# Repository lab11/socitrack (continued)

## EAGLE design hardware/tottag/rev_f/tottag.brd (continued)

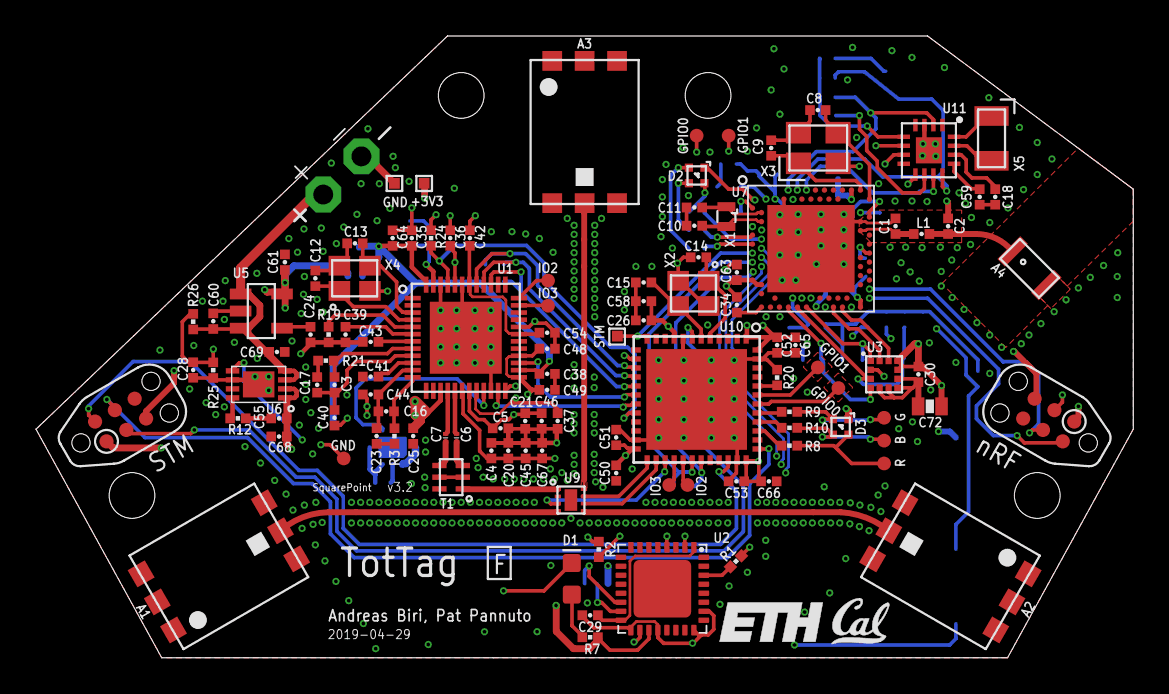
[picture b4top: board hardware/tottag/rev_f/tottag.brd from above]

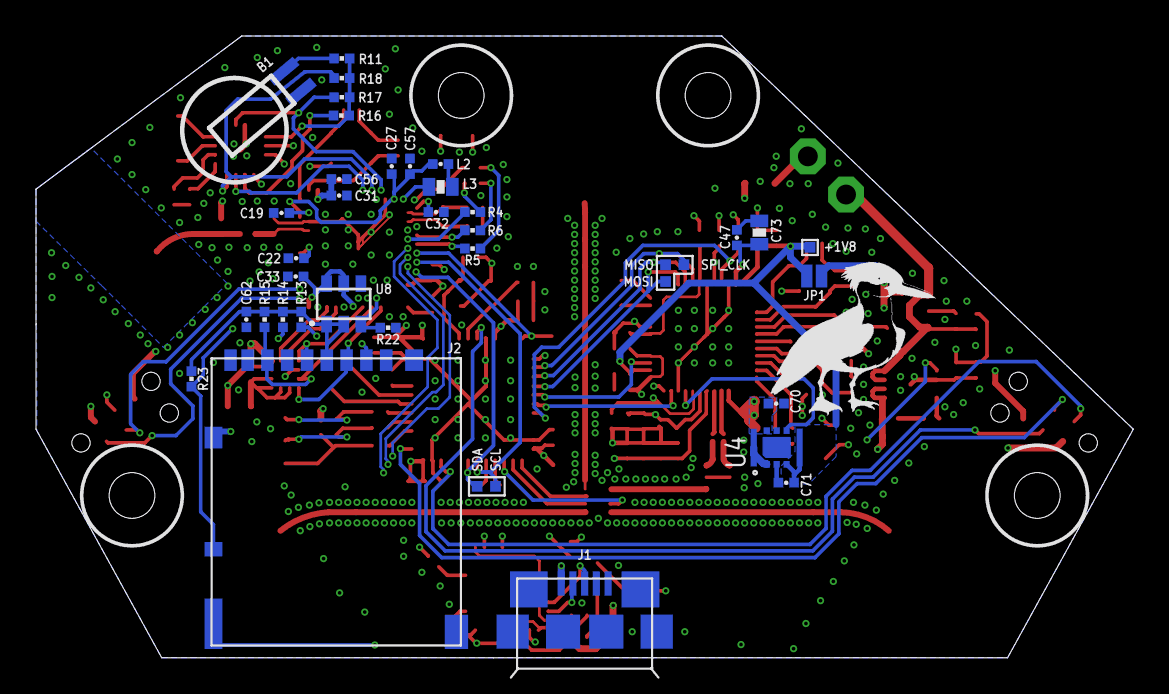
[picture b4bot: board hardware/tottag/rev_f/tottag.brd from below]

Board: 4 copper layers, 61.0 x 34.5 mm, 157 parts (40 on the bottom side), 116 nets.

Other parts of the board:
U$1: TOTTERNARY_300MIL
U$3: ETH_200MIL
U$4: UCB_CAL_100MIL

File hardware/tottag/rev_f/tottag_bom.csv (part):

Qty,Parts,Value,Can Substitute,Do not populate (DNP),Device,Package,Description,DESCRIPTION,DIGIKEY,MANUFACTURER,MPN,MOUSER,Notes
3,"A1,A2,A3",TAIYO-YUDEN-AH086M,N,,TAIYO-YUDEN-AH086M,TAIYO-YUDEN-AH086M,UWB Antenna - 3.1-8GHz,RF ANT 3.5GHZ/5.6GHZ CHIP SLD,587-2204-1-ND,Taiyo Yuden,AH086M555003-T,,
1,A4,ANT3216A063R2400A,N,,ANT3216A063R2400A,ANT3216A063R2400A,Yageo 2.4GHz,RF ANT 2.4GHZ CHIP SOLDER SMD,311-1542-1-ND,Yageo,ANT3216A063R2400A,,
2,"C1,C2",1pF,Y,,CAPACITOR0402_CAP,0402_CAP,SMD Capacitor,CAP CER 1PF 50V C0G/NP0 0402,712-1266-1-ND,Johanson Technology Inc.,500R07S1R0BV4T,,
1,C3,1.2pF,N,,CAPACITOR0402_CAP,0402_CAP,SMD Capacitor,CAP CER 1.2PF 50V C0G/NP0 0402,490-3085-1-ND,Murata Electronics North America,GJM1555C1H1R2CB01D,,
2,"C4,C5",10pF,Y,,CAPACITOR0402_CAP,0402_CAP,SMD Capacitor,CAP CER 10PF 100V C0G/NP0 0402,732-12054-1-ND,Wurth Electronics Inc.,885012005074,,
2,"C6,C7",12pF,N,,CAPACITOR0201_CAP,0201_CAP,SMD Capacitor,CAP CER 12PF 25V C0G/NP0 0201,712-1208-1-ND,Johanson Technology Inc.,250R05L120GV4T,,
8,"C8,C9,C10,C11,C12,C13,C14,C15",12pF,N,,CAPACITOR0402_CAP,0402_CAP,SMD Capacitor,CAP CER 12PF 50V C0G/NP0 0402,490-11190-1-ND,Murata Electronics North America,GJM1555C1H120FB01D,,
1,C16,18pF,N,,CAPACITOR0402_CAP,0402_CAP,SMD Capacitor,CAP CER 18PF 50V C0G/NP0 0402,399-8828-1-ND,KEMET,CBR04C180F5GAC,,
1,C17,27pF,N,,CAPACITOR0402_CAP,0402_CAP,SMD Capacitor,CAP CER 27PF 50V C0G/NP0 0402,490-16380-1-ND,Murata Electronics North America,GJM1555C1H270FB01D,,
1,C18,100pF,Y,,CAPACITOR0402_CAP,0402_CAP,SMD Capacitor,CAP CER SMD 0402 100PF 5% X7R 50,399-17545-1-ND,KEMET,C0402C101J5RACAUTO,,
2,"C19,C20",330pF,Y,,CAPACITOR0402_CAP,0402_CAP,SMD Capacitor,CAP CER 330PF 50V X7R 0402,311-3768-1-ND,Yageo,CC0402JRX7R9BB331,,
2,"C21,C22",820pF,N,,CAPACITOR0402_CAP,0402_CAP,SMD Capacitor,CAP CER 820PF 25V NP0 0402,399-15345-1-ND,KEMET,C0402C821J3GAC7867,,
3,"C23,C24,C25",10nF,Y,,CAPACITOR0402_CAP,0402_CAP,SMD Capacitor,CAP CER 10000PF 25V X7R 0402,399-1279-1-ND,KEMET,C0402C103J3RACTU,,
1,C26,47nF,Y,,CAPACITOR0402_CAP,0402_CAP,SMD Capacitor,CAP CER 0.047UF 16V X7R 0402,445-1264-1-ND,TDK Corporation,C1005X7R1C473K050BC,,
27,"C27,C28,C29,C30,C31,C32,C33,C34,C35,C36,C37,C38,C39,C40,C41,C42,C43,C44,C45,C46,C47,C48,C49,C50,C51,C52,C53",0.1uF,Y,,CAPACITOR0402_CAP,0402_CAP,SMD Capacitor,CAP CER 0.1UF 16V X5R 0402,1276-1234-1-ND,Samsung Electro-Mechanics,CL05A104KO5NNNC,,
4,"C54,C55,C56,C57",1uF,Y,,CAPACITOR0402_CAP,0402_CAP,SMD Capacitor,CAP CER 1UF 10V X6S 0402,1276-6805-1-ND,Samsung Electro-Mechanics,CL05X105KP5NNNC,,
11,"C58,C59,C60,C61,C62,C63,C64,C65,C66,C67,C68",4.7uF,Y,,CAPACITOR0402_CAP,0402_CAP,SMD Capacitor,CAP CER 4.7UF 10V X5R 0402,490-14306-1-ND,Murata Electronics North America,GRM155R61A475MEAAD,,
2,"C69,C70",10uF,Y,,CAPACITOR0603_CAP,0603_CAP,SMD Capacitor,CAP CER 10UF 10V X5R 0603,490-10474-1-ND,Murata Electronics North America,GRM188R61A106KE69D,,
1,C71,47uF,Y,,CAPACITOR0603_CAP,0603_CAP,SMD Capacitor,CAP CER 47UF 6.3V X5R 0603,490-13247-1-ND,Murata Electronics North America,GRM188R60J476ME15D,81-GRM188R60J476ME5D,
1,D1,GREEN,Y,,LED0603,LED-0603,LED (Generic),LED GREEN CLEAR SMD,160-1446-1-ND,Lite-On Inc.,LTST-C191KGKT,,
2,"D2,D3",SML-LX0404SIUPGUSB,Y,,SML-LX0404SIUPGUSB,1MM_SQ_4PAD,1mm^2 RGB LED,LED RGB CLEAR SMD,67-2125-1-ND,Lumex Opto/Components Inc.,SML-LX0404SIUPGUSB,,
1,J1,MICRO_USB_B_HIROSE_ZX62-B-5PA(11),N,,MICRO_USB_B_HIROSE_ZX62-B-5PA(11),USB_MICRO_B-HIROSE-ZX62-B-5PA(11),"Connector Receptacle USB - micro B 2.0 5 Position Surface Mount, Right Angle, Horizontal",CONN MICRO SD CARD PUSH-PUSH R/A,HR1964CT-ND,Hirose Electric Co Ltd,DM3AT-SF-PEJM5,,
1,J2,CON_MICRO_SDDM3AT-SF-PEJM5,N,,CON_MICRO_SDDM3AT-SF-PEJM5,DM3AT-SF-PEJM5,CONN MICRO SD R/A PUSH-PUSH SMD,CONN RCPT USB MICRO B SMD R/A,H125270CT-ND,Hirose Electric Co Ltd,ZX62-B-5PA(33),,
1,L1,3.9nH,Y,,INDUCTOR0402,0402_CAP,A very specific inductor,FIXED IND 3.9NH 840MA 66 MOHM,AISC-0402-3N9G-TCT-ND,Abracon LLC,AISC-0402-3N9G-T,,
1,L2,15nH,Y,,INDUCTOR0402,0402_CAP,A very specific inductor,FIXED IND 15NH 320MA 460 MOHM,587-1521-1-ND,Taiyo Yuden,HK100515NJ-T,,
1,L3,10uH,Y,,INDUCTOR0603,0603_CAP,A very specific inductor,FIXED IND 10UH 300MA 600 MOHM,445-6755-1-ND,TDK Corporation,MLZ1608N100LT000,,
2,"R1,R2",0,Y,,RESISTOR0402_RES,0402_RES,Resistor,RES SMD 0 OHM JUMPER 1/10W 0402,P0.0JCT-ND,Panasonic Electronic Components,ERJ-2GE0R00X,,
1,R3,270,N,,RESISTOR0402_RES,0402_RES,Resistor,RES SMD 270 OHM 1% 1/16W 0402,1276-3970-1-ND,Samsung Electro-Mechanics,RC1005F271CS,,
3,"R4,R5,R6",470,Y,,RESISTOR0402_RES,0402_RES,Resistor,RES SMD 470 OHM 1% 1/16W 0402,541-4072-1-ND,Vishay Dale,CRCW0402470RFKEDC,,
4,"R7,R8,R9,R10",1k,Y,,RESISTOR0402_RES,0402_RES,Resistor,RES SMD 1K OHM 1% 1/5W 0402,541-3240-1-ND,Vishay Dale,RCA04021K00FKEDHP,,
1,R11,2k 1%,Y,,RESISTOR0402_RES,0402_RES,Resistor,RES SMD 2K OHM 1% 1/10W 0402,P2.00KLCT-ND,Panasonic Electronic Components,ERJ-2RKF2001X,,
3,"R12,R13,R14",10k,Y,,RESISTOR0402_RES,0402_RES,Resistor,RES SMD 10K OHM 5% 1/10W 0402,P10KJCT-ND,Panasonic Electronic Components,ERJ-2GEJ103X,,
2,"R15,R16",11k 1%,Y,,RESISTOR0402_RES,0402_RES,Resistor,RES SMD 11K OHM 1% 1/10W 0402,P11.0KLCT-ND,Panasonic Electronic Components,ERJ-2RKF1102X,,
1,R17,16k,N,,RESISTOR0402_RES,0402_RES,Resistor,RES SMD 16K OHM 1% 1/16W 0402,YAG5263CT-ND,Yageo,AC0402FR-0716KL,,
3,"R18,R19,R20",100k,Y,,RESISTOR0402_RES,0402_RES,Resistor,RES SMD 100K OHM 1% 1/16W 0402,541-3960-1-ND,Vishay Dale,CRCW0402100KFKEDC,,
1,R21,2.2M,Y,,RESISTOR0402_RES,0402_RES,Resistor,RES SMD 2.2M OHM 1% 1/16W 0402,541-4083-1-ND,Vishay Dale,CRCW04022M20FKEDC,,
1,R22,10M,Y,,RESISTOR0402_RES,0402_RES,Resistor,RES SMD 10M OHM 5% 1/10W 0402,P10MJCT-ND,Panasonic Electronic Components,ERJ-2GEJ106X,,
1,T1,HHM1595A1,N,,HHM1595A1,EIA-0805,"Description: Symbol for HHM1595A1, a multilayer Balun from TDK.",XFMR BALUN RF 3.0-8.0GHZ UWB SMD,445-3387-1-ND,TDK Corporation,HHM1595A1,,
1,U1,DW1000,N,,DW1000,QFN-48-DW1000,"Description: The DecaWave DW1000 chip, used for UWB two-way ranging.",IC RF TXRX 802.15.4 48-QFN,1479-1001-1-ND,Decawave Limited,DW1000-I-TR13,,
1,U2,FT232RQ,N,,FT232RQ,QFN32,Source: http://www.ftdichip.com/Documents/DataSheets/DS_FT232R_v104.pdf,IC USB FS SERIAL UART 32-QFN,768-1008-1-ND,"FTDI, Future Technology Devices International Ltd",FT232RQ,,
1,U3,LIS2DW12,N,,LIS2DW12,LGA-12,ultra low power 3 axis accelerometer,MEMS DIGITAL OUTPUT MOTION SENSOR,497-17718-6-ND,STMicroelectronics,LIS2DW12TR,,
1,U4,LXDC2HN18A,N,,LXDC2HN18A,LXDC2HN,"Description: Symbol for LXDC2HN18A-097, a DC-DC converter by Murata Electronics.",DC/DC CONVERTER SMD,490-12092-1-ND,Murata Electronics North America,LXDC2HN18A-097,,
1,U5,MAX8887EZK33+T,N,,MAX8887EZK33+T,SOT-23-5,IC REG LDO 3.3V 0.3A TSOT23-5,IC REG LIN 3.3V 300MA TSOT23-5,MAX8887EZK33+TCT-ND,Maxim Integrated,MAX8887EZK33+T,,
1,U6,MCP73831,N,,MCP73831,DFN-8-MCP,"Description: Device for MCP73831, a battery charge controller from Microchip.",IC CONTROLLER LI-ION 4.2V 8DFN,MCP73831T-2ACI/MCCT-ND,Microchip Technology,MCP73831T-2ACI/MC,,
1,U7,NRF52840,N,,NRF52840,AQFN73,"ultra-low power 2.4 GHz wireless system on chip (SoC) integrating a multiprotocol 2.4 GHz transceiver, an ARM® Cortex®-M4F CPU.",NRF52840-QIAA QFN 73L,1490-1071-1-ND,Nordic Semiconductor ASA,NRF52840,,
1,U8,SIP32510,N,,SIP32510,TSOT23-6,"Load switch, slew rate controlled. By Vishay",IC LOAD SWITCH SOT23-6, SIP32510DT-T1-GE3CT-ND,Vishay Siliconix,SIP32510DT-T1-GE3,,
1,U9,SKY13317,N,,SKY13317,MLPQ-UT-8,"Description: Device for SKY13317-373LF, an RF switch from Skyworks Inc.",IC SWITCH RF SP3T 8-MLP,863-1056-1-ND,Skyworks Solutions Inc.,SKY13317-373LF,,
1,U10,STM32F091CC,N,,STM32F091CC,UFQFPN-48,"Description: STM32F091CC from STMicroelectronics, an ARM-based 32-bit MCU with 256 kB Flash, 32kB of SRAM and a Cortex M0",IC MCU 32BIT 256KB FLASH 48QFPN,497-15813-ND,STMicroelectronics,STM32F091CCU6,,
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
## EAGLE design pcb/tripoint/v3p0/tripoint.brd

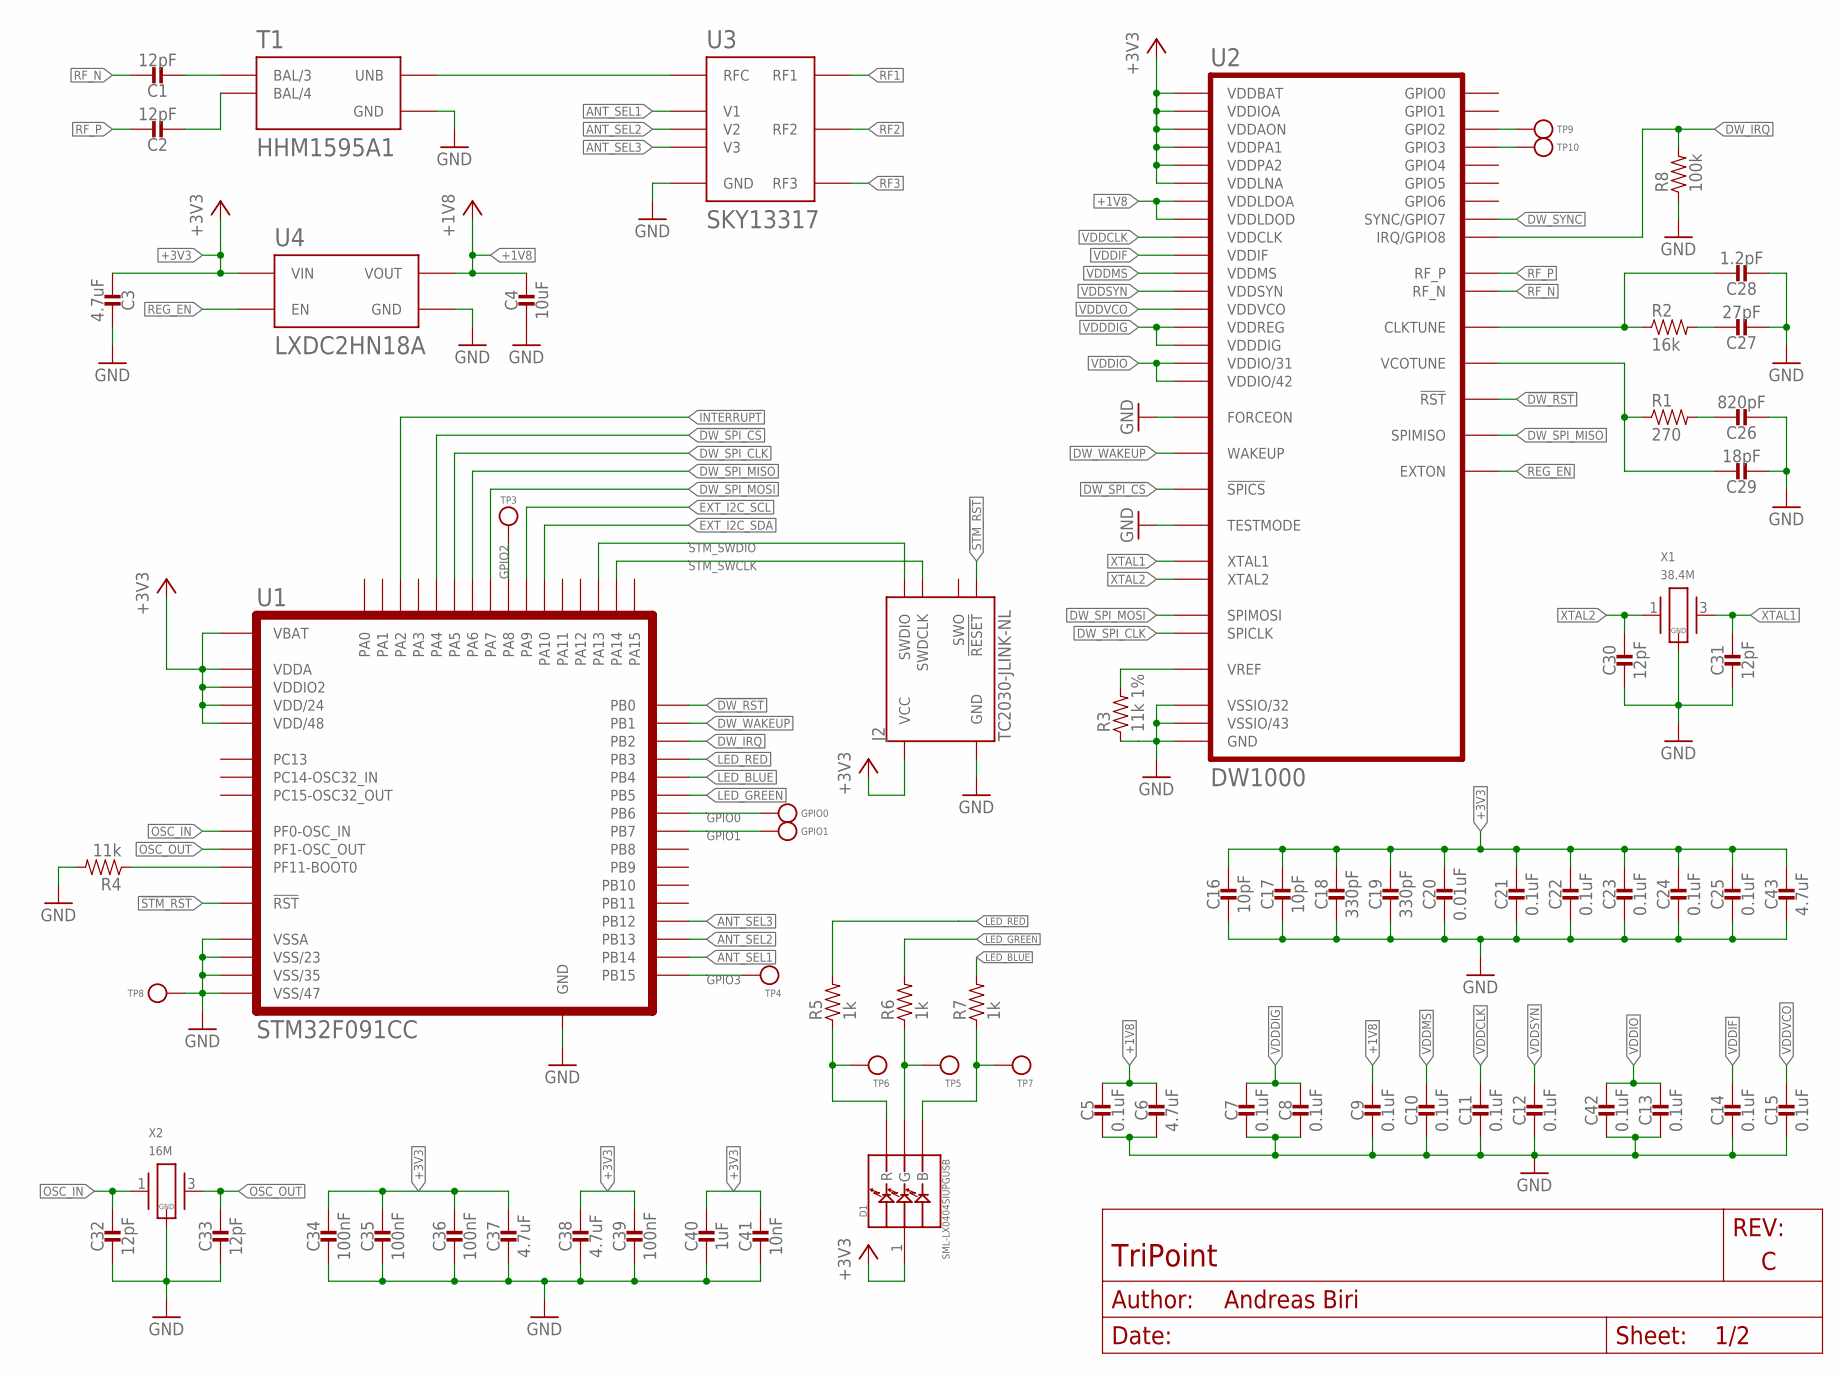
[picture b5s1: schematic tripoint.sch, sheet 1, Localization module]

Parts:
C1, C2: 12pF; 0201_CAP
C3, C6, C37, C38, C43: 4.7uF; 0402_CAP
C4: 10uF; 0603_CAP
C5, C7, C8, C9, C10, C11, C12, C13, C14, C15, C21, C22, C23, C24, C25, C42: 0.1uF; 0402_CAP
C16, C17: 10pF; 0402_CAP
C18, C19: 330pF; 0402_CAP
C20: 0.01uF; 0402_CAP
C26: 820pF; 0402_CAP
C27: 27pF; 0402_CAP
C28: 1.2pF; 0402_CAP
C29: 18pF; 0402_CAP
C30, C31, C32, C33: 12pF; 0402_CAP
C34, C35, C36, C39: 100nF; 0402_CAP
C40: 1uF; 0402_CAP
C41: 10nF; 0402_CAP
D1: SML-LX0404SIUPGUSB; 1MM_SQ_4PAD
GPIO0, GPIO1: TEST_POINT_0.040IN; TESTPOINT_0.040IN
J2: TC2030-JLINK-NL; TC2030-IDC-NL
R1: 270; 0402_RES
R2: 16k; 0402_RES
R3: 11k 1%; 0402_RES
R4: 11k; 0402_RES
R5, R6, R7: 1k; 0402_RES
R8: 100k; 0402_RES
T1: HHM1595A1; EIA-0805
TP3, TP4, TP5, TP6, TP7, TP8, TP9, TP10: TEST-POINT; PAD.03X.03
U1: STM32F091CC; UFQFPN-48
U2: DW1000; QFN-48-DW1000
U3: SKY13317; MLPQ-UT-8
U4: LXDC2HN18A; LXDC2HN
X1: 38.4M; FA-20H; DIGIKEY SER3631CT-ND
X2: 16M; FA-20H; DIGIKEY SER3913CT-ND

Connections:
!DW_RST: U1.18 (PB0), U2.27 (!RST)
!DW_SPI_CS: U1.14 (PA4), U2.24 (!SPICS)
!STM_RST: J2.3 (!RESET), U1.7 (!RST)
+1V8: C4.1, C5.1, C6.1, C9.1, U2.26 (VDDLDOD), U2.48 (VDDLDOA), U4.3 (VOUT)
+3V3: C3.2, C16.1, C17.1, C18.1, C19.1, C20.1, C21.1, C22.1, C23.1, C24.1, C25.1, C34.1, C35.1, C36.1, C37.1, C38.1, C39.1, C40.1, C41.1, C43.1, D1.1 (VDD), J2.1 (VCC), U1.1 (VBAT), U1.9 (VDDA), U1.24 (VDD/24), U1.36 (VDDIO2), U1.48 (VDD/48), U2.15 (VDDLNA), U2.18 (VDDPA1), U2.19 (VDDPA2), U2.25 (VDDAON), U2.28 (VDDIOA), U2.47 (VDDBAT), U4.1 (VIN)
ANT_SEL1: U1.27 (PB14), U3.3 (V1)
ANT_SEL2: U1.26 (PB13), U3.6 (V2)
ANT_SEL3: U1.25 (PB12), U3.7 (V3)
DW_IRQ: R8.2, U1.20 (PB2), U2.45 (IRQ/GPIO8)
DW_SPI_CLK: U1.15 (PA5), U2.41 (SPICLK)
DW_SPI_MISO: U1.16 (PA6), U2.40 (SPIMISO)
DW_SPI_MOSI: U1.17 (PA7), U2.39 (SPIMOSI)
DW_SYNC: U2.29 (SYNC/GPIO7)
DW_WAKEUP: U1.19 (PB1), U2.23 (WAKEUP)
EXT_I2C_SCL: U1.30 (PA9)
EXT_I2C_SDA: U1.31 (PA10)
GND: C3.1, C4.2, C5.2, C6.2, C7.2, C8.2, C9.2, C10.2, C11.2, C12.2, C13.2, C14.2, C15.2, C16.2, C17.2, C18.2, C19.2, C20.2, C21.2, C22.2, C23.2, C24.2, C25.2, C26.2, C27.2, C28.2, C29.2, C30.2, C31.2, C32.2, C33.2, C34.2, C35.2, C36.2, C37.2, C38.2, C39.2, C40.2, C41.2, C42.2, C43.2, J2.5 (GND), R3.1, R4.2, R8.1, T1.2 (GND), T1.5 (GND), TP8.P$1, U1.8 (VSSA), U1.23 (VSS/23), U1.35 (VSS/35), U1.47 (VSS/47), U1.GND, U2.22 (FORCEON), U2.32 (VSSIO/32), U2.43 (VSSIO/43), U2.46 (TESTMODE), U2.GND, U3.GND, U4.4 (GND), X1.2 (GND), X1.4 (GND), X2.2 (GND), X2.4 (GND)
GPIO0: GPIO0.TESTPOINT, U1.42 (PB6)
GPIO1: GPIO1.TESTPOINT, U1.43 (PB7)
GPIO2: TP3.P$1, U1.29 (PA8)
GPIO3: TP4.P$1, U1.28 (PB15)
INTERRUPT: U1.12 (PA2)
LED_BLUE: R7.2, U1.40 (PB4)
LED_GREEN: R6.2, U1.41 (PB5)
LED_RED: R5.2, U1.39 (PB3)
unnamed: T1.1 (UNB), U3.1 (RFC)
unnamed: C1.P$2 (2), T1.3 (BAL/3)
unnamed: C2.P$2 (2), T1.4 (BAL/4)
unnamed: C26.1, R1.2
unnamed: C27.1, R2.2
unnamed: C29.1, R1.1, U2.12 (VCOTUNE)
unnamed: R3.2, U2.5 (VREF)
unnamed: R4.1, U1.44 (PF11-BOOT0)
unnamed: C28.1, R2.1, U2.8 (CLKTUNE)
unnamed: D1.4 (G), R6.1, TP5.P$1
unnamed: D1.3 (B), R7.1, TP7.P$1
unnamed: D1.2 (R), R5.1, TP6.P$1
unnamed: TP9.P$1, U2.36 (GPIO2)
unnamed: TP10.P$1, U2.35 (GPIO3)
OSC_IN: C32.1, U1.5 (PF0-OSC_IN), X2.1
OSC_OUT: C33.1, U1.6 (PF1-OSC_OUT), X2.3 (2)
REG_EN: U2.21 (EXTON), U4.2 (EN)
RF1: U3.4 (RF1)
RF2: U3.5 (RF2)
RF3: U3.8 (RF3)
RF_N: C1.P$1 (1), U2.17 (RF_N)
RF_P: C2.P$1 (1), U2.16 (RF_P)
STM_SWCLK: J2.4 (SWDCLK), U1.37 (PA14)
STM_SWDIO: J2.2 (SWDIO), U1.34 (PA13)
VDDCLK: C11.1, U2.9 (VDDCLK)
VDDDIG: C7.1, C8.1, U2.20 (VDDREG), U2.44 (VDDDIG)
VDDIF: C14.1, U2.7 (VDDIF)
VDDIO: C13.1, C42.1, U2.31 (VDDIO/31), U2.42 (VDDIO/42)
VDDMS: C10.1, U2.6 (VDDMS)
VDDSYN: C12.1, U2.10 (VDDSYN)
VDDVCO: C15.1, U2.11 (VDDVCO)
XTAL1: C31.1, U2.3 (XTAL1), X1.3 (2)
XTAL2: C30.1, U2.4 (XTAL2), X1.1

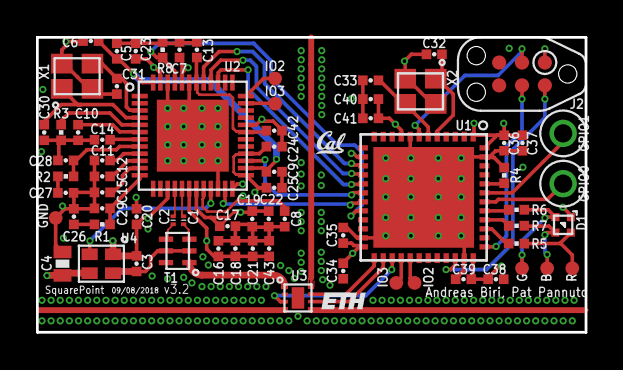
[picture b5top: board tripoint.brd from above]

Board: 4 copper layers, 30.5 x 16.4 mm, 72 parts (0 on the bottom side), 51 nets.

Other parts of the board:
U$1: ETH_100MIL
U$2: UCB_CAL_50MIL

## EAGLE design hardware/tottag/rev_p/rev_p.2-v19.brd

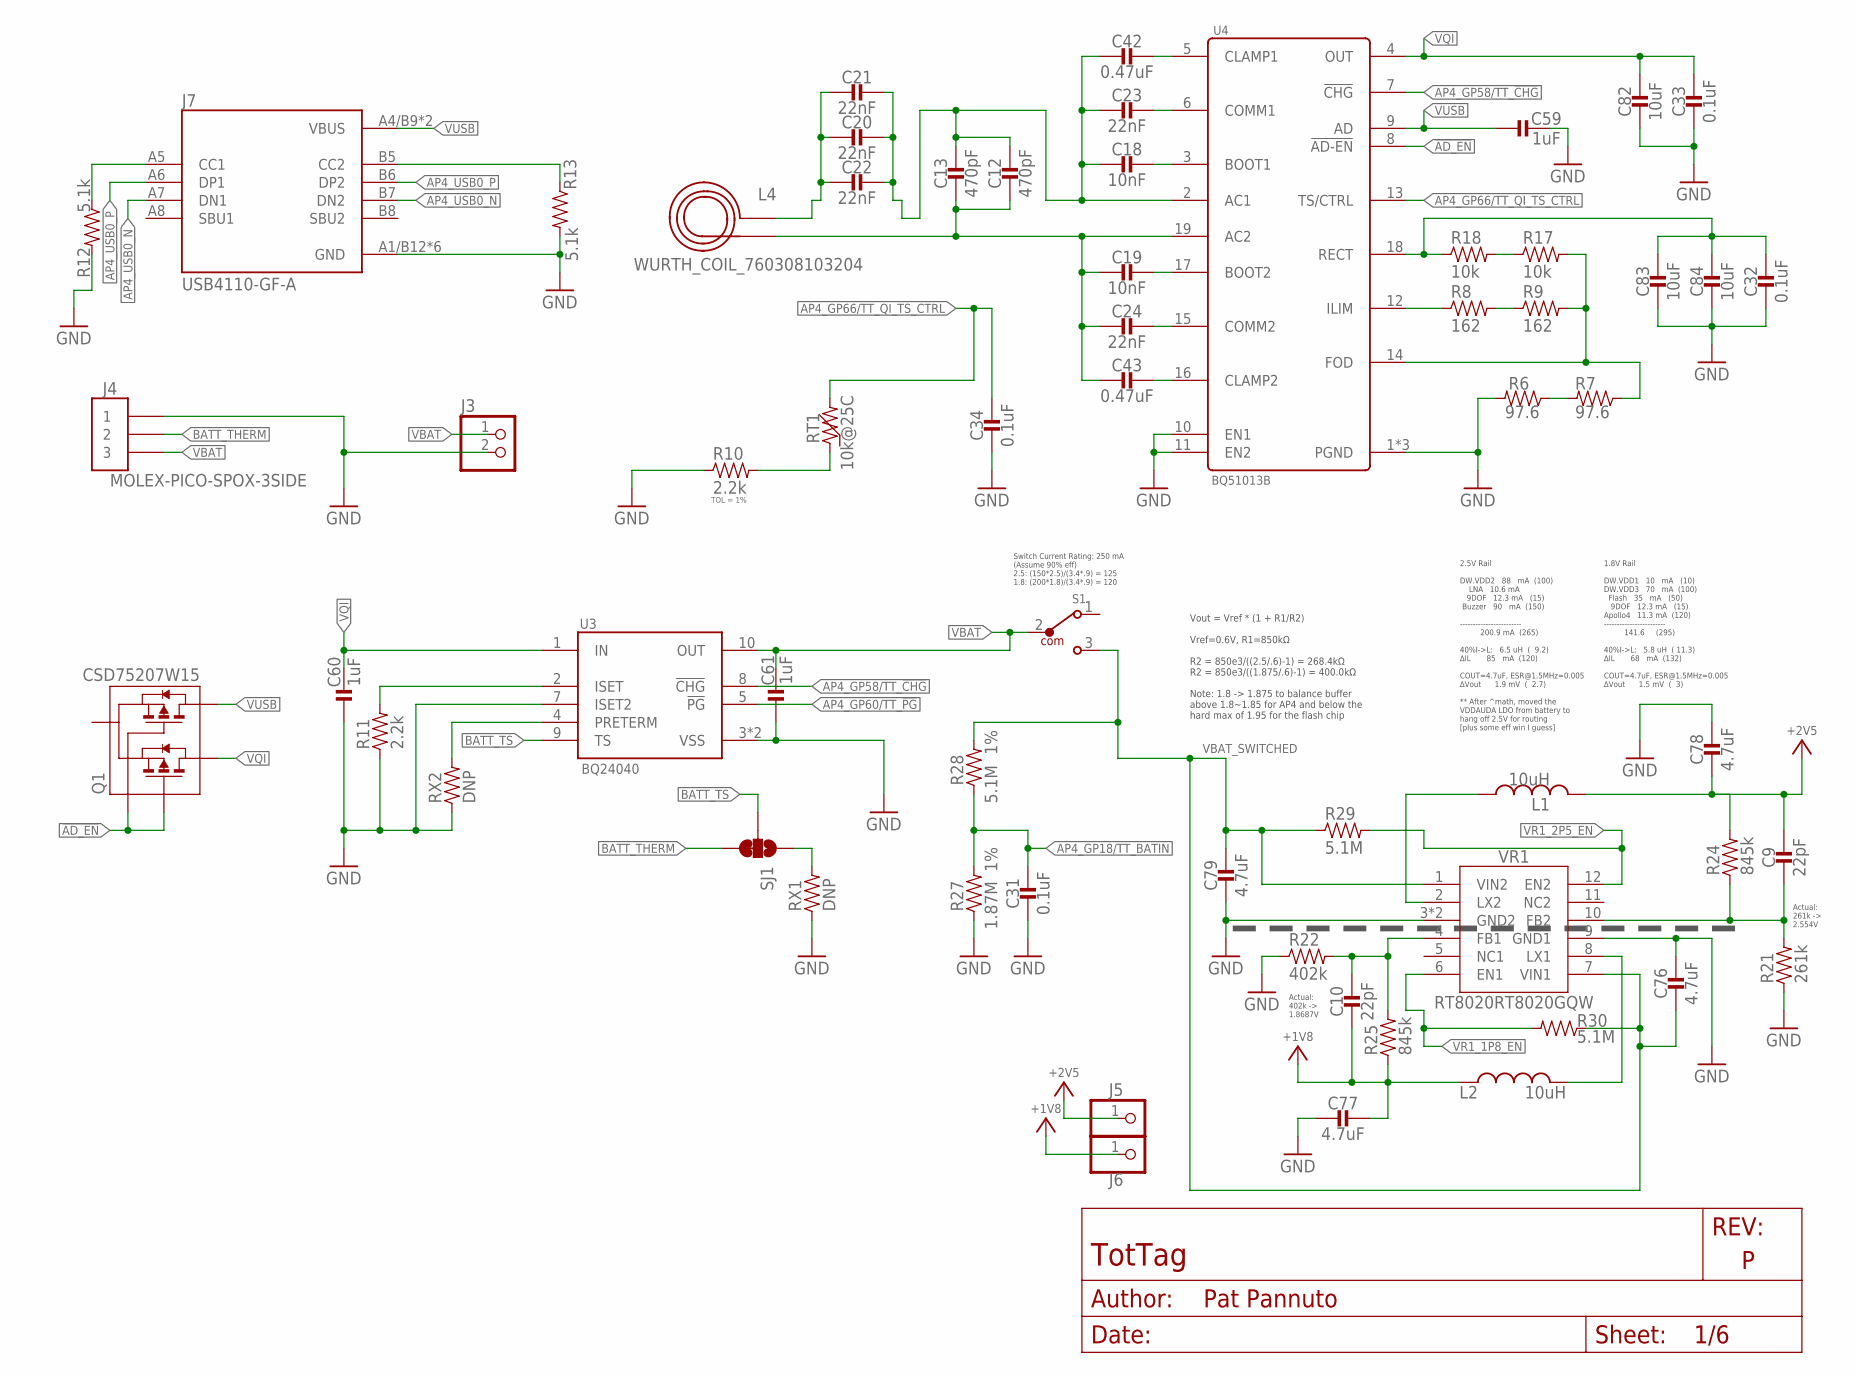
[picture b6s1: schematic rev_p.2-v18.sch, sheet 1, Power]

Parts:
C9, C10: 22pF; 0201_CAP; MPN GRM0335C1H220FA01D
C12, C13: 470pF; 0402_CAP; MPN GRM1555C1H471JA01J; DIGIKEY 490-6242-1-ND
C18, C19: 10nF; 0402_CAP; MPN GRM155R71H103KA88J; DIGIKEY 490-6351-2-ND
C20, C21, C22: 22nF; 0402_CAP; MPN GRM155R71E223JA61D; DIGIKEY 490-10699-2-ND
C23, C24: 22nF; 0402_CAP; MPN CC0402ZRY5V8BB223; DIGIKEY 311-3823-1-ND
C31, C32, C33, C34: 0.1uF; 0402_CAP; MPN GRM155R71C104KA88J; DIGIKEY 490-6328-1-ND
C42, C43: 0.47uF; 0402_CAP; MPN C1005X5R1E474K050BB
C59, C60, C61: 1uF; 0201_CAP; MPN GRM033R61A105ME44D
C76, C77, C78, C79: 4.7uF; 0603_CAP; MPN C1608X7S1A475K080AC
C82, C83, C84: 10uF; 0603_CAP; MPN CM105X5R106M25AT; DIGIKEY 1253-CM105X5R106M25ATCT-ND
J3: PINHD-1X2; 1X02
J4: MOLEX-PICO-SPOX-3SIDE; MOLEX-PICO-SPOX-3_SIDE
J5, J6: PINHD-1X1; 1X01
J7: USB4110-GF-A; GCT_USB4110-GF-A
L1, L2: 10uH; NRX3015; MPN NR3015T100M
L4: WURTH_COIL_760308103204
Q1: CSD75207W15; DSBGA
R6, R7: 97.6; 0402_RES; MPN RMCF0402FT97R6; DIGIKEY RMCF0402FT97R6CT-ND
R8, R9: 162; 0402_RES; MPN RMCF0402FT162R; DIGIKEY RMCF0402FT162RCT-ND
R10, R11: 2.2k; 0402_RES; MPN RC0402FR-072K2L
R12, R13: 5.1k; 0402_RES; MPN RMCF0402FT5K10; DIGIKEY RMCF0402FT5K10CT-ND
R17, R18: 10k; 0402_RES; MPN RC0402JR-0710KL; DIGIKEY 311-10KJRCT-ND
R21: 261k; 0201_RES; MPN ERJ-1GNF2613C
R22: 402k; 0201_RES; MPN ERJ-1GNF4023C
R24, R25: 845k; 0201_RES; MPN ERJ-1GNF8453C
R27: 1.87M; 0402_RES; TOLERANCE 1%; MPN RMCF0402FT1M87
R28: 5.1M; 0402_RES; TOLERANCE 1%; MPN RMCF0402FT5M10; DIGIKEY RMCF0402FT5M10CT-ND
R29, R30: 5.1M; 0402_RES; MPN RMCF0402FT5M10; DIGIKEY RMCF0402FT5M10CT-ND
RT1: 10k@25C; 0402_RES; MPN NCU15XH103F60RC; DIGIKEY 490-18149-1-ND
RX1, RX2: DNP; 0402_RES
S1: 450404015514; DIGIKEY 732-13665-1-ND
SJ1: JUMPER-SMT_3_1-NC_TRACE_SILK; SMT-JUMPER_3_1-NC_TRACE_SILK
U3: BQ24040; DSQ0010A
U4: BQ51013B; RHL0020A
VR1: RT8020RT8020GQW; SON45P300X300X80-13T160X250N

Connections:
!AD_EN: Q1.A1 (G1), Q1.C1 (G2), U4.8 (!AD-EN)
+1V8: C10.P$2 (2), C77.1, J6.1, L2.P$1 (1), R25.1; also elsewhere on the board
+2V5: C9.P$1 (1), C78.2, J5.1, L1.P$2 (2), R24.2; also elsewhere on the board
AP4_GP18/TT_BATIN: C31.1, R27.2, R28.1; also elsewhere on the board
AP4_GP58/TT_!CHG: U3.8 (!CHG), U4.7 (!CHG); also elsewhere on the board
AP4_GP60/TT_!PG: U3.5 (!PG); also elsewhere on the board
AP4_GP66/TT_QI_TS_CTRL: C34.1, RT1.2, U4.13 (TS/CTRL); also elsewhere on the board
AP4_USB0_N: J7.A7 (DN1), J7.B7 (DN2); also elsewhere on the board
AP4_USB0_P: J7.A6 (DP1), J7.B6 (DP2); also elsewhere on the board
BATT_THERM: J4.2, J4.2SUPP (2), SJ1.3
BATT_TS: SJ1.2, U3.9 (TS)
BQ_AC1: C12.1, C13.1, C18.2, C20.1, C21.1, C22.1, C23.2, C42.2, U4.2 (AC1)
BQ_AC2: C12.2, C13.2, C19.2, C24.2, C43.2, L4.P$2 (2), U4.19 (AC2)
BQ_BOOT1: C18.1, U4.3 (BOOT1)
BQ_BOOT2: C19.1, U4.17 (BOOT2)
BQ_CLAMP1: C42.1, U4.5 (CLAMP1)
BQ_CLAMP2: C43.1, U4.16 (CLAMP2)
BQ_COMM1: C23.1, U4.6 (COMM1)
BQ_COMM2: C24.1, U4.15 (COMM2)
BQ_FOD: R7.1, R9.2, R17.2, U4.14 (FOD)
BQ_ILM: R8.1, U4.12 (ILIM)
BQ_ISET: R11.2, U3.2 (ISET)
BQ_RECT: C32.1, C83.1, C84.1, R18.1, U4.18 (RECT)
COIL_AC1: C20.2, C21.2, C22.2, L4.P$1 (1)
GND: C31.2, C32.2, C33.2, C34.2, C59.P$2 (2), C60.P$1 (1), C61.P$1 (1), C76.1, C77.2, C78.1, C79.2, C82.2, C83.2, C84.2, J3.2, J4.1, J4.1SUPP (1), J7.A1/B12 (GND), J7.B1/A12 (GND), J7.S1 (GND), J7.S2 (GND), J7.S3 (GND), J7.S4 (GND), R6.2, R10.1, R11.1, R12.2, R13.2, R21.1, R22.1, R27.1, RX1.1, RX2.1, U3.3 (VSS), U3.7 (ISET2), U3.PAD (VSS), U4.1 (PGND), U4.10 (EN1), U4.11 (EN2), U4.20 (PGND), U4.PAD (PGND), VR1.3 (GND2), VR1.9 (GND1), VR1.13 (GND2); also elsewhere on the board
unnamed: R6.1, R7.2
unnamed: RX1.2, SJ1.1
unnamed: RX2.2, U3.4 (PRETERM)
unnamed: R17.1, R18.2
unnamed: R8.2, R9.1
unnamed: R10.2, RT1.1
USB_CC1: J7.A5 (CC1), R12.1
USB_CC2: J7.B5 (CC2), R13.1
VBAT: C61.P$2 (2), J3.1, J4.3, J4.3SUPP (3), S1.2, U3.10 (OUT)
VBAT_SWITCHED: C76.2, C79.1, R28.2, R29.1, R30.1, S1.3, VR1.1 (VIN2), VR1.7 (VIN1); also elsewhere on the board
VQI: C33.1, C60.P$2 (2), C82.1, Q1.A2 (D1), Q1.A3 (D1), Q1.B3 (D1), U3.1 (IN), U4.4 (OUT)
VR1_1P8_EN: R30.2, VR1.6 (EN1)
VR1_2P5_EN: R29.2, VR1.12 (EN2)
VR1_FB1: C10.P$1 (1), R22.2, R25.2, VR1.4 (FB1)
VR1_FB2: C9.P$2 (2), R21.2, R24.1, VR1.10 (FB2)
VR1_LX1: L2.P$2 (2), VR1.8 (LX1)
VR1_LX2: L1.P$1 (1), VR1.2 (LX2)
VUSB: C59.P$1 (1), J7.A4/B9 (VBUS), J7.B4/A9 (VBUS), Q1.B2 (D2), Q1.C2 (D2), Q1.C3 (D2), U4.9 (AD); also elsewhere on the board

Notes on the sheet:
2.5V Rail DW.VDD2 88 mA (100) LNA 10.6 mA 9DOF 12.3 mA (15) Buzzer 90 mA (150) ------------------------ 200.9 mA (265) 40%I->L: 6.5 uH ( 9.2) ∆IL 85 mA (120) COUT=4.7uF, ESR@1.5MHz=0.005 ∆Vout 1.9 mV ( 2.7) ** After ^math, moved the VDDAUDA LDO from battery to hang off 2.5V for routing [plus some e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
1.8V Rail DW.VDD1 10 mA (10) DW.VDD3 70 mA (100) Flash 35 mA (50) 9DOF 12.3 mA (15) Apollo4 11.3 mA (120) ------------------------ 141.6 (295) 40%I->L: 5.8 uH ( 11.3) ∆IL 68 mA (132) COUT=4.7uF, ESR@1.5MHz=0.005 ∆Vout 1.5 mV ( 3)
Vout = Vref * (1 + R1/R2) Vref=0.6V, R1=850kΩ R2 = 850e3/((2.5/.6)-1) = 268.4kΩ R2 = 850e3/((1.875/.6)-1) = 400.0kΩ Note: 1.8 -> 1.875 to balance buffer above 1.8~1.85 for AP4 and below the hard max of 1.95 for the flash chip
Switch Current Rating: 250 mA (Assume 90% eff) 2.5: (150*2.5)/(3.4*.9) = 125 1.8: (200*1.8)/(3.4*.9) = 120
Actual: 402k -> 1.8687V
Actual: 261k -> 2.554V

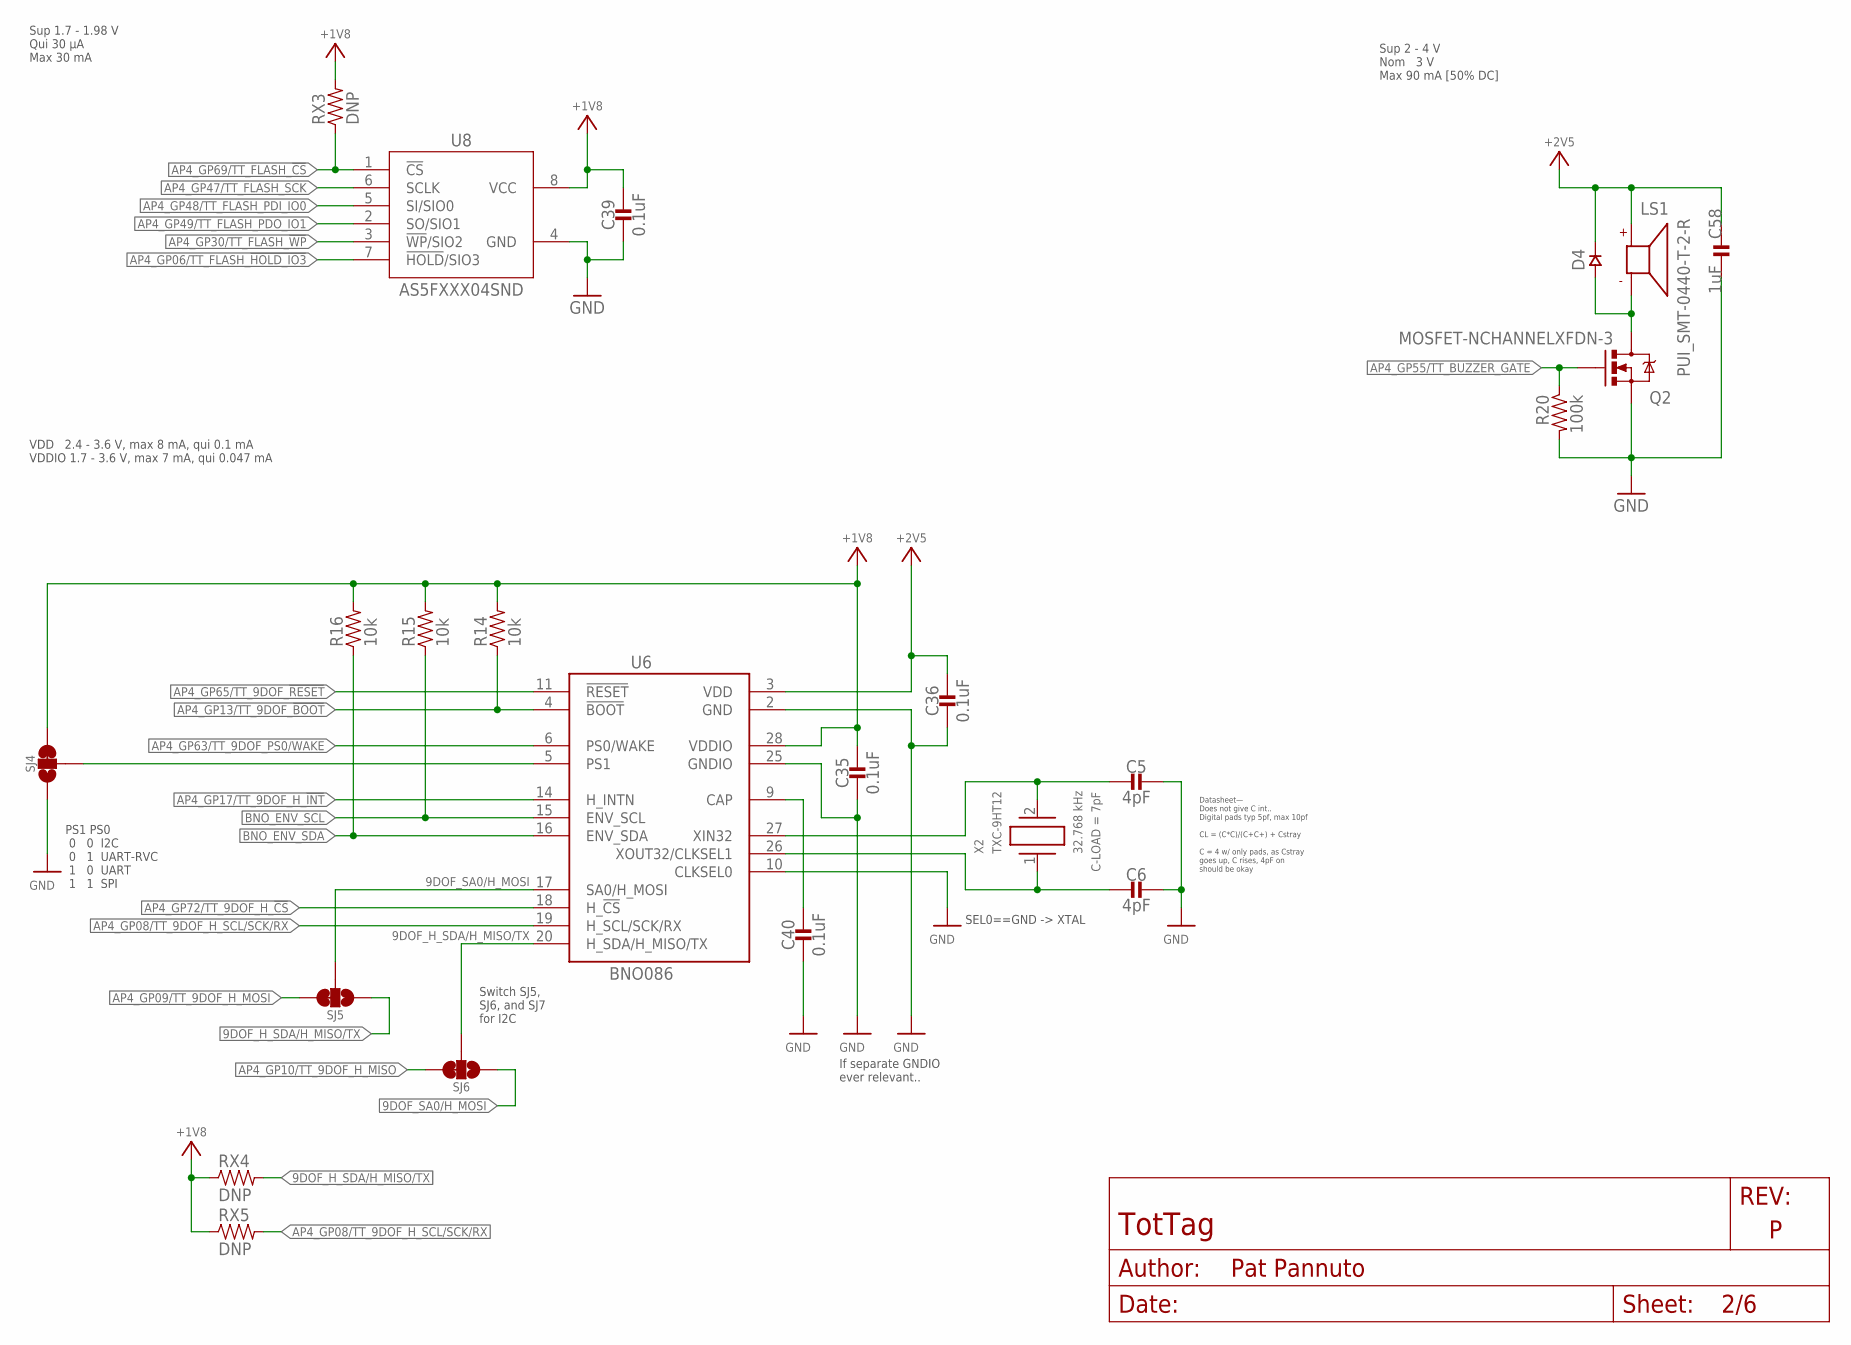
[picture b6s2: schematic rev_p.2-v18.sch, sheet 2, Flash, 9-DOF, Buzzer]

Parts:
C5, C6: 4pF; 0201_CAP; MPN GRM0335C1H4R0BA01D
C35, C36, C39, C40: 0.1uF; 0402_CAP; MPN CL05A104KP5NNNC
C58: 1uF; 0201_CAP; MPN GRM033R61A105ME44D
D4: DIODE0402; 0402_DIODE; MPN CDSQR400B-HF; DIGIKEY 641-2087-1-ND
LS1: PUI_SMT-0440-T-2-R; SMT-0440-T-2-R
Q2: MOSFET-NCHANNELXFDN-3; XFDFN-3
R14, R15, R16: 10k; 0402_RES; MPN RC0402JR-0710KL; DIGIKEY 311-10KJRCT-ND
R20: 100k; 0402_RES; MPN RT0402BRE07100KL
RX3, RX4, RX5: DNP; 0603-RES
SJ4, SJ5, SJ6: JUMPER-SMT_3_1-NC_TRACE_SILK; SMT-JUMPER_3_1-NC_TRACE_SILK
U6: BNO086; LGA28R0P510X4_5P2X3P8X1
U8: AS5FXXX04SND; AS5FXXXXXXXX-XXLXN
X2: TXC-9HT12; MPN 9HT12-32.768KDZY-T

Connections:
9DOF_CAP: C40.1, U6.9 (CAP)
9DOF_H_SDA/H_MISO/TX: RX4.2, SJ5.1, SJ6.2, U6.20 (H_SDA/H_MISO/TX)
9DOF_SA0/H_MOSI: SJ5.2, SJ6.1, U6.17 (SA0/H_MOSI)
9DOF_XI: C5.P$2 (2), U6.27 (XIN32), X2.2
9DOF_XO: C6.P$2 (2), U6.26 (XOUT32/CLKSEL1), X2.1
+1V8: C35.1, C39.1, R14.2, R15.2, R16.2, RX3.2, RX4.1, RX5.1, SJ4.3, U6.28 (VDDIO), U8.8 (VCC); also elsewhere on the board
+2V5: C36.1, C58.P$1 (1), D4.CATHODE, LS1.+, U6.3 (VDD); also elsewhere on the board
AP4_GP06/TT_FLASH_!HOLD_IO3: U8.7 (!HOLD!/SIO3); also elsewhere on the board
AP4_GP08/TT_9DOF_H_SCL/SCK/RX: RX5.2, U6.19 (H_SCL/SCK/RX); also elsewhere on the board
AP4_GP09/TT_9DOF_H_MOSI: SJ5.3; also elsewhere on the board
AP4_GP10/TT_9DOF_H_MISO: SJ6.3; also elsewhere on the board
AP4_GP13/TT_9DOF_!BOOT: R14.1, U6.4 (!BOOT); also elsewhere on the board
AP4_GP17/TT_9DOF_H_!INT: U6.14 (H_INTN); also elsewhere on the board
AP4_GP30/TT_FLASH_!WP: U8.3 (!WP!/SIO2); also elsewhere on the board
AP4_GP47/TT_FLASH_SCK: U8.6 (SCLK); also elsewhere on the board
AP4_GP48/TT_FLASH_PDI_IO0: U8.5 (SI/SIO0); also elsewhere on the board
AP4_GP49/TT_FLASH_PDO_IO1: U8.2 (SO/SIO1); also elsewhere on the board
AP4_GP55/TT_BUZZER_GATE: Q2.G, R20.1; also elsewhere on the board
AP4_GP63/TT_9DOF_PS0/WAKE: U6.6 (PS0/WAKE); also elsewhere on the board
AP4_GP65/TT_9DOF_!RESET: U6.11 (!RESET); also elsewhere on the board
AP4_GP69/TT_FLASH_!CS: RX3.1, U8.1 (!CS); also elsewhere on the board
AP4_GP72/TT_9DOF_H_!CS: U6.18 (H_!CS); also elsewhere on the board
BNO_ENV_SCL: R15.1, U6.15 (ENV_SCL)
BNO_ENV_SDA: R16.1, U6.16 (ENV_SDA)
BNO_PS1: SJ4.2, U6.5 (PS1)
GND: C5.P$1 (1), C6.P$1 (1), C35.2, C36.2, C39.2, C40.2, C58.P$2 (2), Q2.S, R20.2, SJ4.1, U6.2 (GND), U6.10 (CLKSEL0), U6.25 (GNDIO), U8.4 (GND); also elsewhere on the board
unnamed: D4.ANODE, LS1.- (N), Q2.D

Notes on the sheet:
Sup 1.7 - 1.98 V Qui 30 µA Max 30 mA
VDD 2.4 - 3.6 V, max 8 mA, qui 0.1 mA VDDIO 1.7 - 3.6 V, max 7 mA, qui 0.047 mA
Sup 2 - 4 V Nom 3 V Max 90 mA [50% DC]
If separate GNDIO ever relevant..
Datasheet— Does not give C int.. Digital pads typ 5pf, max 10pf CL = (C*C)/(C+C+) + Cstray C = 4 w/ only pads, as Cstray goes up, C rises, 4pF on should be okay
SEL0==GND -> XTAL
PS1 PS0 0 0 I2C 0 1 UART-RVC 1 0 UART 1 1 SPI
Switch SJ5, SJ6, and SJ7 for I2C
